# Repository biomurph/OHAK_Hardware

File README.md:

# OHAK_Hardware
Place for OHAK prototypes

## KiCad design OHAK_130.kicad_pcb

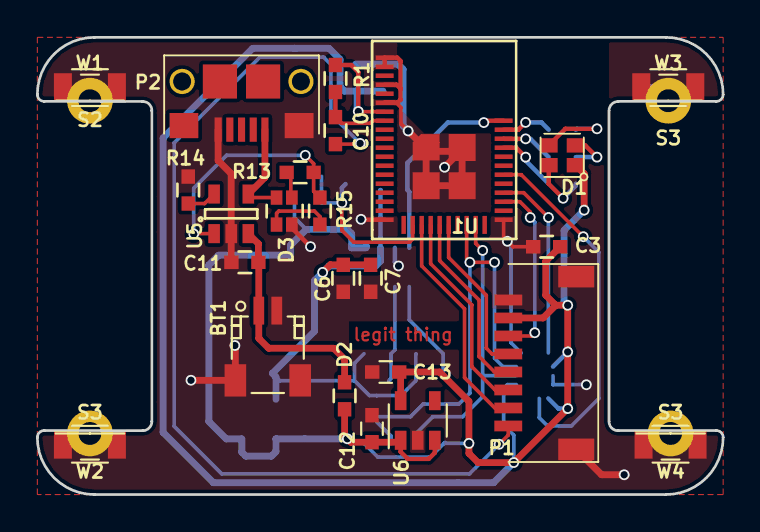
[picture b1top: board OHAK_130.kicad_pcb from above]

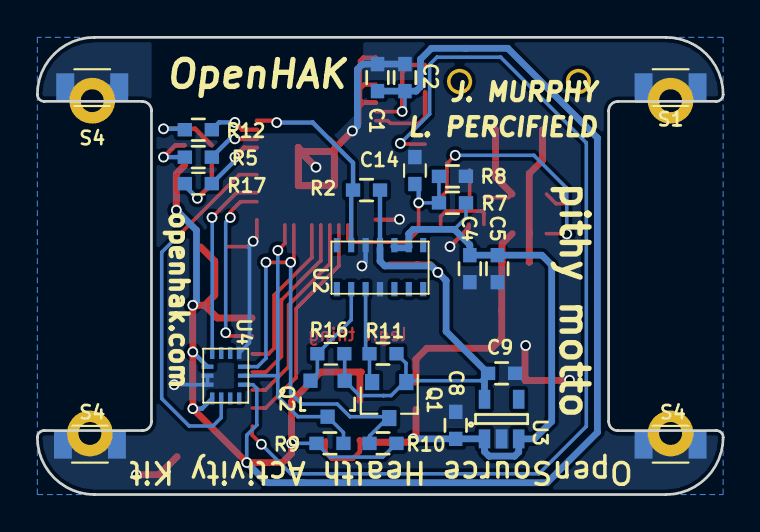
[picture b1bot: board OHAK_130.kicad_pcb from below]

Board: 2 copper layers, 38.1 x 25.4 mm, 54 parts (26 on the bottom side), 31 nets.

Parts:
BT1: Battery; JST_SH_SM02B-SRSS-TB_02x1.00mm_Angled
C1, C7, C10: 0.1uF; C_0603
C2, C4, C6, C8, C9, C12, C13, C14: 1uF; C_0603
C3, C5, C11: 10uF; C_0603
D1: Led_RGB_CA; CLMVB-FKA-CFHEHLCBB7a363
D2: D_Schottky; C_0603
D3: Dialight_R_G_LED; 0606_Bi-Color
P1: CONN_01X10; 4u-0201GDVE06
P2: USB_OTG; 10118193_microUSB
Q1, Q2: Q_NMOS_GSD; SOT-23
R1, R2, R9, R10, R11, R14, R16: 10K; C_0603
R5: 130R; C_0603
R7, R8: 1M; C_0603
R12, R17: 30R; C_0603
R13, R15: 470; C_0603
S1, S2, S3, S3#2, S3#3, S4, S4#2, S4#3: C_1206
U1: rfd_77101; RFD77101
U2: MAX30100
U3, U6: NCP551; SOT-23-5
U4: BMI160; LGA_2.5x3
U5: MCP73831; SOT-23-5
W1, W2, W3, W4: Watch_Pin_50mil

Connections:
+1V8: C6.1, C7.2, C9.2, Q1.1, Q2.1, R2.1, R11.2, R16.2, U2.11, U3.5
/1V8_SCL: Q2.2, R16.1, U2.2
/1V8_SDA: Q1.2, R11.1, U2.3
/3V3_SCL: Q2.3, R9.1, U1.28, U4.13
/3V3_SDA: Q1.3, R10.1, U1.27, U4.14
/BMI_INT1: U1.33, U4.4
/BMI_INT2: U1.35, U4.9
/B_LED: R17.2, U1.38
/G_LED: R12.2, U1.40
/MAX_INT: R2.2, U1.41, U2.13
/PIN_2: P1.4, U1.24
/PIN_3: P1.2, U1.22
/PIN_4: P1.6, U1.32
/R_LED: R5.2, U1.39
/SIM_RST: C10.1, R1.2, U1.8
/SIM_RX: P1.5, U1.25
/SIM_TX: P1.3, U1.23
/V_SENSE: C14.2, R7.1, R8.2, U1.21
GND: BT1.2, C1.1, C2.1, C3.1, C4.2, C5.2, C6.2, C7.1, C8.1, C9.1, C11.1, C12.1, C13.1, C14.1, D3.2, P1.8, P1.9, P1.10, P2.5, P2.6, R8.1, R14.2, S1.1, S1.2, S2.1, S2.2, S3.1, S3.2, S3#2.1, S3#2.2, S3#3.1, S3#3.2, S4.1, S4.2, S4#2.1, S4#2.2, S4#3.1, S4#3.2, U1.1, U1.2, U1.4, U1.6, U1.19, U1.30, U1.42, U1.43, U1.44, U1.45, U2.4, U2.12, U3.2, U4.1, U4.6, U4.7, U5.2, U6.2, W1.1, W2.1, W3.1, W4.1
unnamed: BT1.1, C11.2, D2.2, U5.3
unnamed: C10.2, P1.1
unnamed: D1.2, R17.1
unnamed: D1.3, R12.1
unnamed: D1.4, R5.1
unnamed: D3.1, R13.2
unnamed: D3.3, P2.1, U5.4
unnamed: D3.4, R15.2
unnamed: R13.1, R15.1, U5.1
unnamed: R14.1, U5.5
VDD: C1.2, C2.2, C3.2, C13.2, D1.1, P1.7, R1.1, R9.2, R10.2, U1.7, U4.5, U4.8, U4.12, U6.5
VPP: C4.1, C5.1, C8.2, C12.2, D2.1, R7.2, U2.9, U2.10, U3.1, U3.3, U6.1, U6.3

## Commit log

2019-02-13 added smaller parts to the PCB. Needs layout.
2019-02-13 updated shematic and library
2019-02-13 Moving things around
2019-02-15 moved parts to top layer and routed board
2019-02-15 Updated library files
2019-03-29 tidying up a bit
2019-03-29 finish tidying up
2019-04-18 updating BOM
2019-04-18 finished BOM
2019-05-03 fixed mis pinned part. moved stuff around
2019-05-06 FIXED BREAKS IN COPPER POURS
2019-05-06 resixed solder mask aperature
2019-05-06 plotted gerbers
2019-05-31 minor changes
2019-05-31 Updated with latest designs
2020-09-15 update to current
